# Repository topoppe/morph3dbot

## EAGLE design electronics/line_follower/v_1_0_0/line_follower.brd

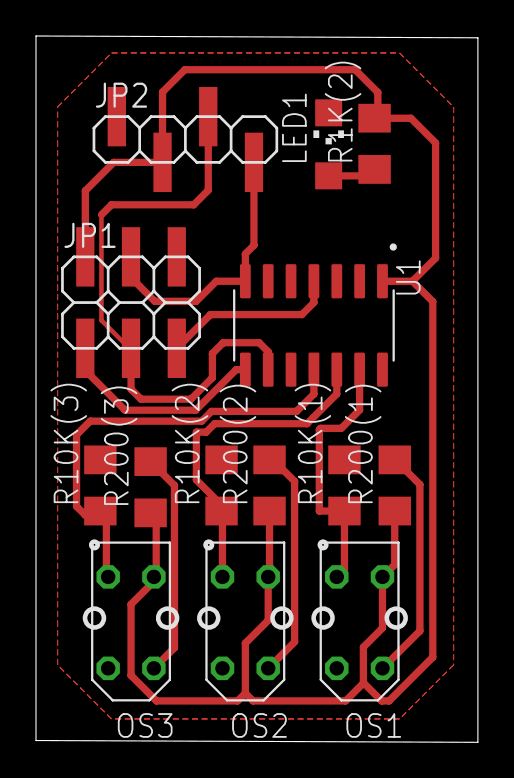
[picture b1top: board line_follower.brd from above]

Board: 2 copper layers, 24.6 x 39.2 mm, 14 parts (0 on the bottom side), 13 nets.

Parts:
JP1: 2X03SMD
JP2: 1X04SMD
LED1: CHIPLED_1206
OS1, OS2, OS3: TCRT5000
R1K(2), R10K(1), R10K(2), R10K(3), R200(1), R200(2), R200(3): R1206
U1: ATTINY44A-SSU; SOIC127P600X175-14N

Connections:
GND: JP1.6, JP2.1, LED1.C, OS1.K, OS2.K, OS3.K, R10K(1).2, R10K(2).2, R10K(3).2, U1.14
unnamed: OS1.E, R10K(1).1, U1.13
unnamed: LED1.A, R1K(2).1
unnamed: JP1.4, JP2.4, U1.7
unnamed: OS2.E, R10K(2).1, U1.12
unnamed: JP1.1, U1.8
unnamed: OS3.E, R10K(3).1, U1.11
unnamed: JP1.5, U1.4
unnamed: OS1.A, R200(1).2
unnamed: JP1.3, JP2.3, U1.9
unnamed: OS2.A, R200(2).2
unnamed: OS3.A, R200(3).2
VCC: JP1.2, JP2.2, OS1.C, OS2.C, OS3.C, R1K(2).2, R200(1).1, R200(2).1, R200(3).1, U1.1

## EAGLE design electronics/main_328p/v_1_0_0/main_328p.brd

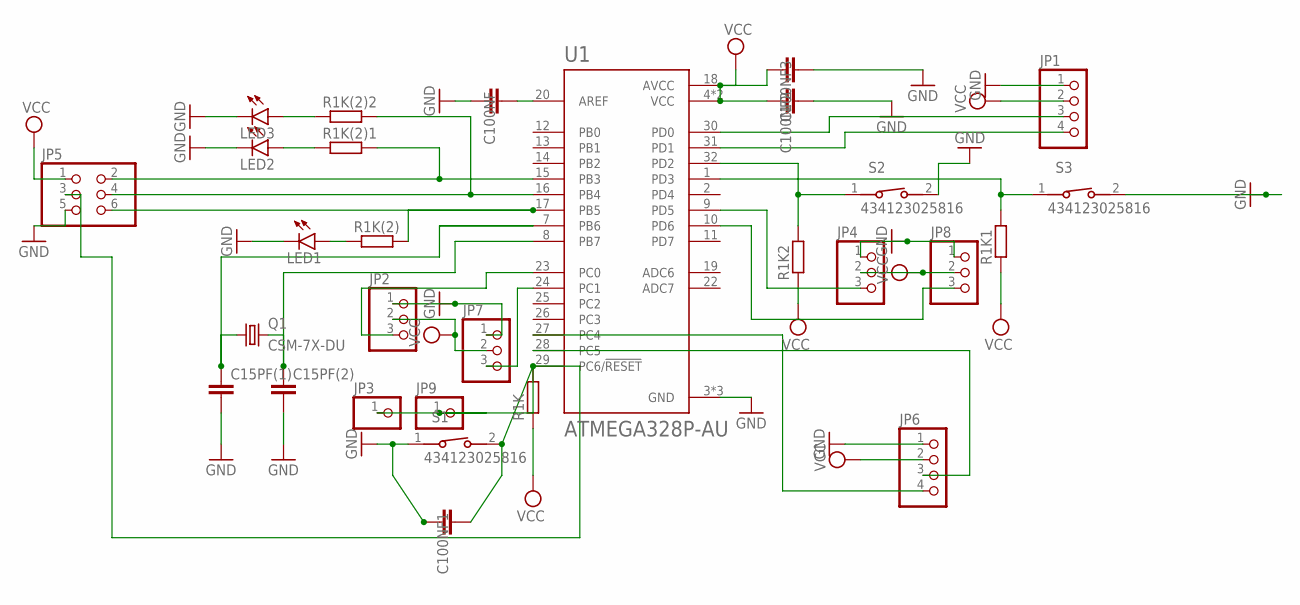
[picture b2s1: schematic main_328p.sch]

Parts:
C15PF(1), C15PF(2), C100NF, C100NF1, C100NF2, C100NF3: C-EUC0603; C0603
JP1, JP6: PINHD-1X04_2.54-SMD; 1X04SMD
JP2, JP4, JP7, JP8: PINHD-1X03_2.54-SMD; 1X03SMD
JP3, JP9: PINHD-1X01_2.54; 1X01
JP5: PINHD-2X03_2.54-SMD; 2X03SMD
LED1, LED2, LED3: LEDCHIPLED_1206; CHIPLED_1206
Q1: CSM-7X-DU
R1K, R1K1, R1K2, R1K(2), R1K(2)1, R1K(2)2: R-EU_R1206; R1206
S1, S2, S3: 434123025816
U1: ATMEGA328P-AU; QFP80P900X900X120-32N

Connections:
GND: C15PF(1).2, C15PF(2).2, C100NF.1, C100NF1.1, C100NF2.2, C100NF3.2, JP1.1, JP2.1, JP4.1, JP5.5, JP6.1, JP7.1, JP8.1, LED1.C, LED2.C, LED3.C, S1.1, S2.2, S3.2, U1.3 (GND), U1.5 (GND), U1.21 (GND)
unnamed: JP2.3, U1.23 (PC0)
unnamed: C15PF(1).1, Q1.1, U1.7 (PB6)
unnamed: LED1.A, R1K(2).1
unnamed: C100NF.2, U1.20 (AREF)
unnamed: JP7.3, U1.24 (PC1)
unnamed: JP5.6, R1K(2).2, U1.17 (PB5)
unnamed: LED3.A, R1K(2)2.1
unnamed: LED2.A, R1K(2)1.1
unnamed: JP6.4, U1.27 (PC4)
unnamed: C15PF(2).1, Q1.2, U1.8 (PB7)
unnamed: JP6.3, U1.28 (PC5)
unnamed: R1K2.2, S2.1, U1.32 (PD2)
unnamed: JP5.2, R1K(2)1.2, U1.15 (PB3)
unnamed: R1K1.2, S3.1, U1.1 (PD3)
unnamed: JP1.3, U1.30 (PD0)
unnamed: JP1.4, U1.31 (PD1)
unnamed: JP4.3, U1.9 (PD5)
unnamed: JP8.3, U1.10 (PD6)
unnamed: C100NF1.2, JP3.1, JP5.3, JP9.1, R1K.2, S1.2, U1.29 (PC6/!RESET)
unnamed: JP5.4, R1K(2)2.2, U1.16 (PB4)
VCC: C100NF2.1, C100NF3.1, JP1.2, JP2.2, JP4.2, JP5.1, JP6.2, JP7.2, JP8.2, R1K.1, R1K1.1, R1K2.1, U1.4 (VCC), U1.6 (VCC), U1.18 (AVCC)

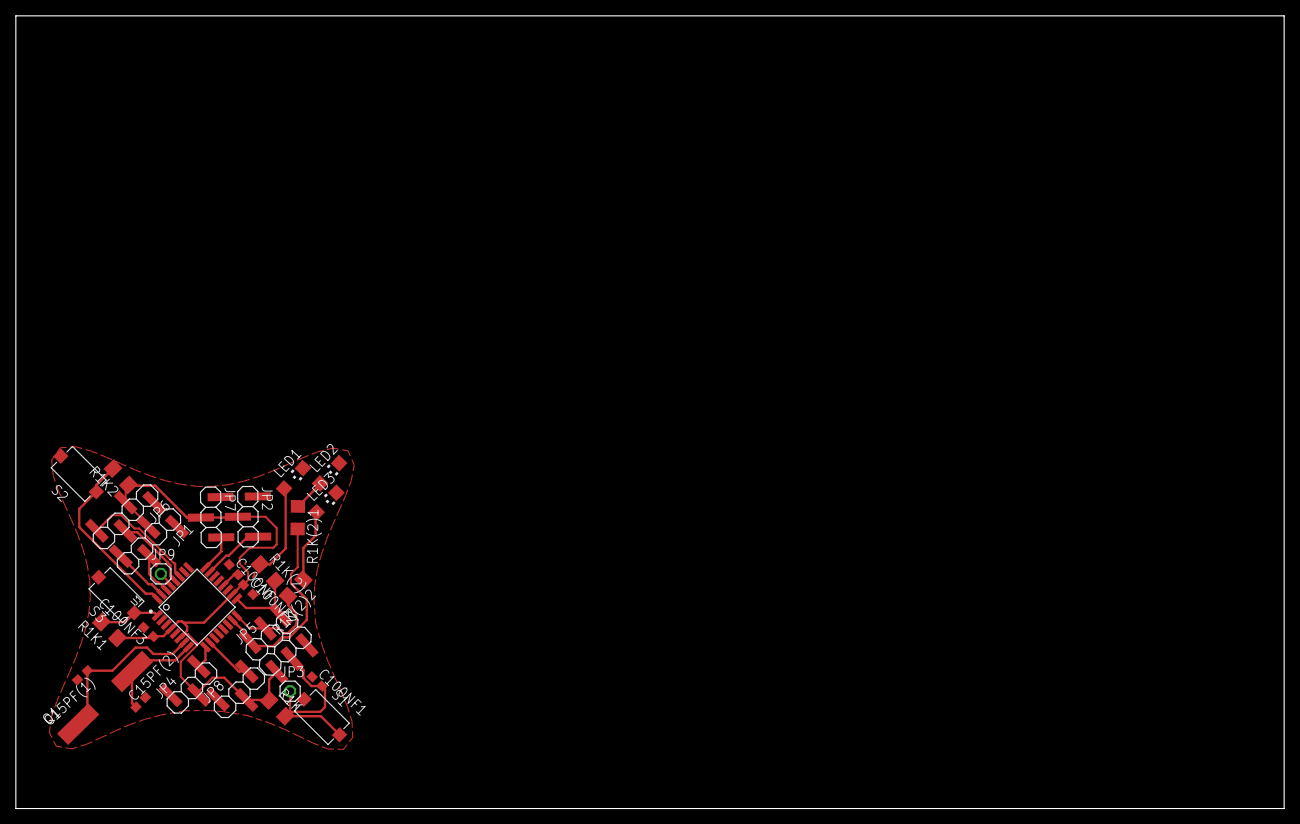
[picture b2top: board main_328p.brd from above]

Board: 2 copper layers, 160.0 x 100.0 mm, 29 parts (0 on the bottom side), 22 nets.

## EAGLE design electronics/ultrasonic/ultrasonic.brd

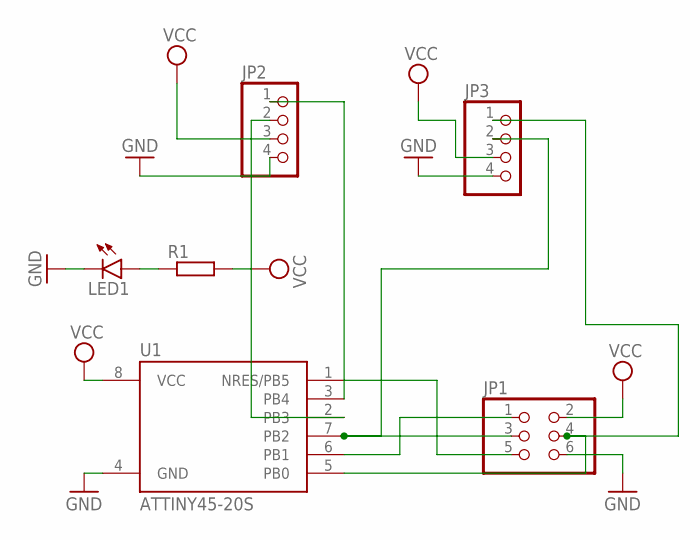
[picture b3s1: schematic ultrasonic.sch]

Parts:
JP1: PINHD-2X03_2.54-SMD; 2X03SMD
JP2, JP3: PINHD-1X04_2.54-SMD; 1X04SMD
LED1: LEDCHIPLED_1206; CHIPLED_1206
R1: R-EU_R1206; R1206
U1: ATTINY45-20S; SOIC8_EIAJ_208MIL

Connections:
GND: JP1.6, JP2.4, JP3.4, LED1.C, U1.4 (GND)
unnamed: LED1.A, R1.1
unnamed: JP2.1, U1.3 (PB4)
unnamed: JP1.4, JP3.1, U1.5 (PB0)
unnamed: JP1.1, U1.6 (PB1)
unnamed: JP1.5, U1.1 (NRES/PB5)
unnamed: JP1.3, JP3.2, U1.7 (PB2)
unnamed: JP2.2, U1.2 (PB3)
VCC: JP1.2, JP2.3, JP3.3, R1.2, U1.8 (VCC)

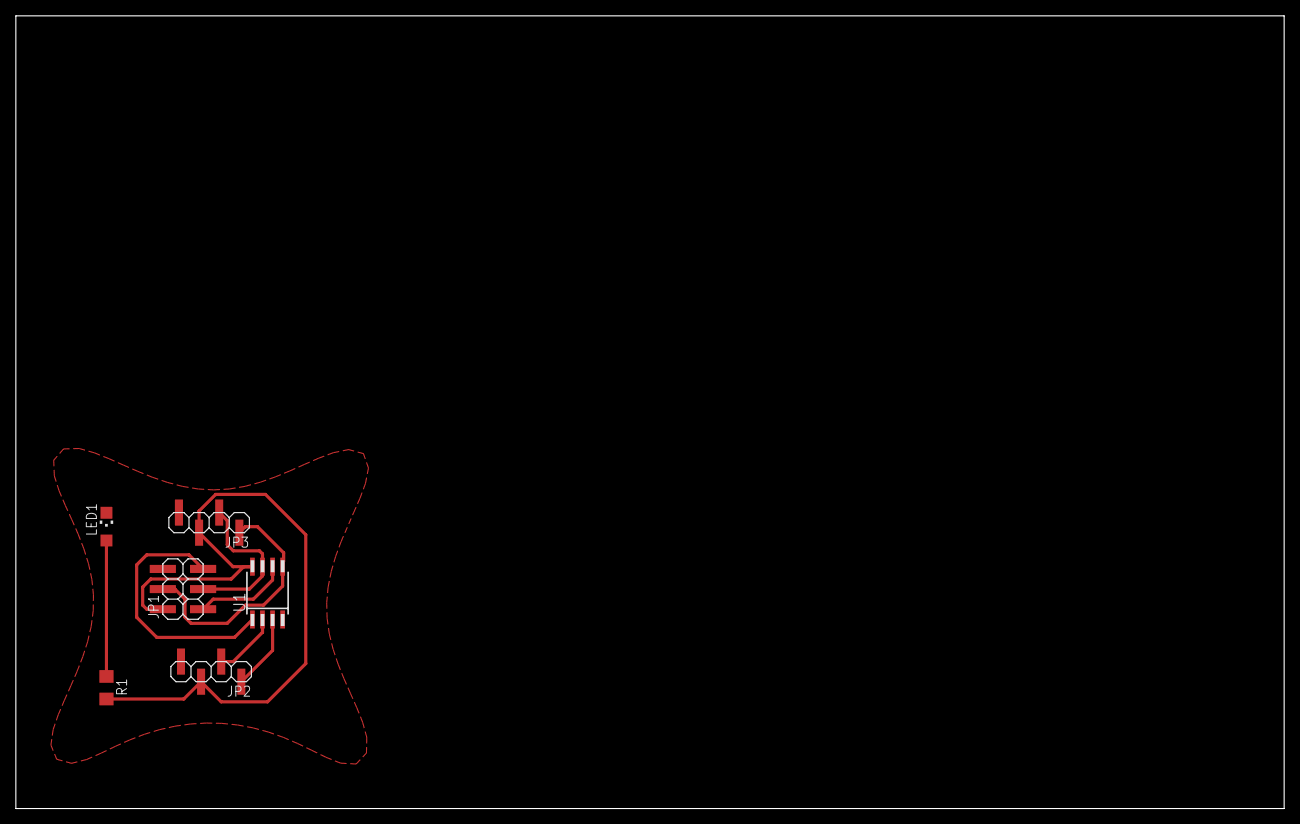
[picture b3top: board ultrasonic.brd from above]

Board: 2 copper layers, 160.0 x 100.0 mm, 6 parts (0 on the bottom side), 9 nets.
